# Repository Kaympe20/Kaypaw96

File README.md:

# Kaypaw96

<br>

A Southpaw 96% keyboard because numpads on the left are awesome
* They allow the keyboard to be centered on your desk.
* They let you use the mouse and numpad at the same time.
* They are plain more ergonomic.

---

[As featured on](https://highway.hackclub.com/projects/kaympe20/kaypaw96)

---

I made this keyboard because, as an ambidextrous person, I often feel like my left hand is under-utilized while I am doing productivity, coding, and gaming. I also use a 75% and sometimes miss having more keys, so I wanted to make a keyboard that gave you nearly every key of a regular keyboard, plus 4 additional macro keys for things like sleep.

## Pics

## CAD

The entire CAD workspace can be found on [Onshape](https://cad.onshape.com/documents/bc15378757c65db7b8fb3e3b/w/9f716e622823b7e5e5c4b7e3/e/b78d5af8ee98cae8cd027468?renderMode=0&uiState=688afe042b679217b95b0b97)

## BOM

| Item | Quantity | Price | Price After Taxes + Shipping |
|------|----------|-------|------------------------------|
[Assembled PCB](https://github.com/Kaympe20/Kaypaw96/tree/main/production) | 1 | $81.58 | $169.13
[3D Printed Case](https://github.com/Kaympe20/Kaypaw96/blob/main/cad/Case.step) | 1 | $0 | $0
[Cherry MX Switches](https://www.amazon.com/Glorious-Gaming-Hotswappable-Mechanical-Keyboards/dp/B0DCPCS6CP) (cheapest I could find after shipping) | 110 | $31.99 | $33.91
[Keycap Set](https://www.amazon.com/Keycaps-Doubleshot-Percent-Mechanical-Keyboard/dp/B0D1QVD55F) | 1 | $16.86 | $17.87
[NCP1117-3.3_SOT223](https://www.amazon.com/PMMCON-AMS1117-LM1117-Voltage-Regulator/dp/B0BNY8KM87) | 1 | $9.99 | $10.59
[M3 Hardware](https://www.amazon.com/420pcs-Premium-Printing-Assortment-Washers/dp/B0CSX4NX7R) | N/a | $6.99 | $7.41

Total: $238.91

Here's the parts I selected in JLCPCB:

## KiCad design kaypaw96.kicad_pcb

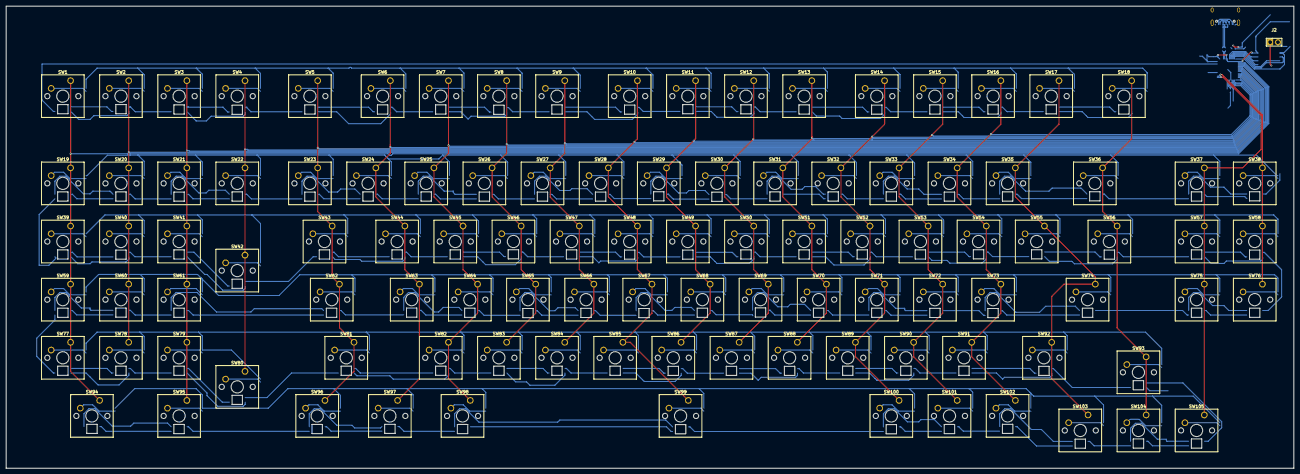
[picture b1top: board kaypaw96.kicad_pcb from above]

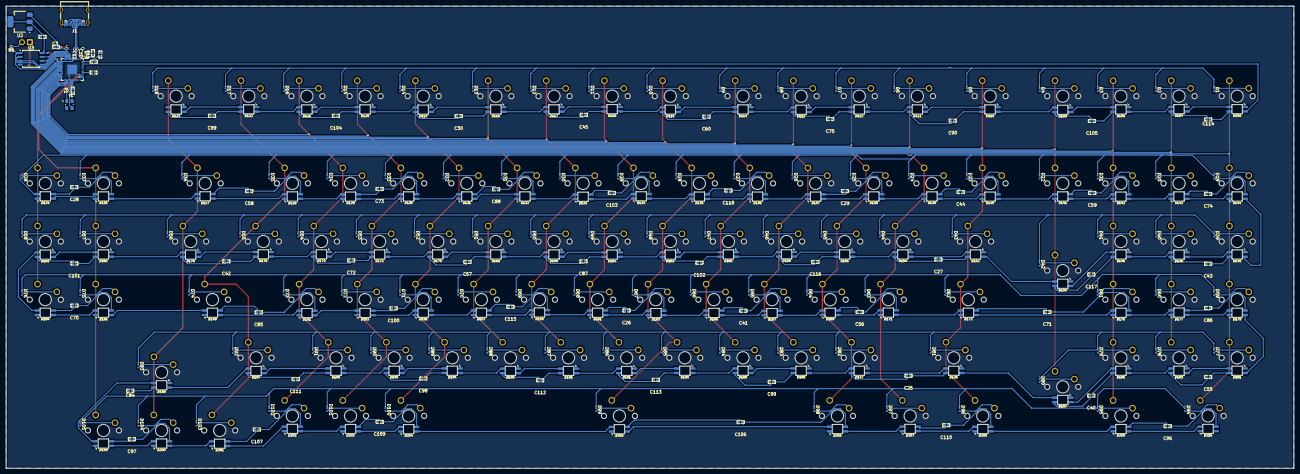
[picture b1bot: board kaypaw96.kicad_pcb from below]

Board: 2 copper layers, 421.9 x 151.4 mm, 388 parts (282 on the bottom side), 256 nets.

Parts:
C3: 10u; C0402
C8, C9, C10, C11, C12, C13, C14: 100n; C0402
C25, C26, C27, C28, C29, C30, C40, C41, C42, C43, C44, C45, C55, C56, C57, C58, C59, C60, C70, C71, C72, C73, C74, C75, C84, C85, C86, C87, C88, C89, C90, C96, C97, C98, C99, C100, C101, C102, C103, C104, C105, C106, C107, C109, C110, C111, C112, C113, C114, C115, C116, C117, C118: 0.1u; C0402
D1, D2, D3, D4, D5, D6, D7, D8, D9, D10, D11, D12, D13, D14, D15, D16, D17, D18, D19, D20, D21, D22, D23, D24, D25, D26, D27, D28, D29, D30, D31, D32, D33, D34, D35, D36, D37, D38, D39, D40, D41, D42, D43, D44, D45, D46, D47, D48, D49, D50, D51, D52, D53, D54, D55, D56, D57, D58, D59, D60, D61, D62, D63, D64, D65, D66, D67, D68, D69, D70, D71, D72, D73, D74, D75, D76, D77, D78, D79, D80, D81, D82, D83, D84, D85, D86, D87, D88, D89, D90, D91, D92, D93, D94, D95, D96, D97, D98, D99, D100, D101, D102, D103, D104, D105: D; RB161QS-40
D106, D107, D108, D109, D110, D111, D112, D113, D114, D115, D116, D117, D118, D119, D120, D121, D122, D123, D124, D125, D126, D127, D128, D129, D130, D131, D132, D133, D134, D135, D136, D137, D138, D139, D140, D141, D142, D143, D144, D145, D146, D147, D148, D149, D150, D151, D152, D153, D154, D155, D156, D157, D158, D159, D160, D161, D162, D163, D164, D165, D166, D167, D168, D169, D170, D171, D172, D173, D174, D175, D176, D177, D178, D179, D180, D181, D182, D183, D184, D185, D186, D187, D188, D189, D190, D191, D192, D193, D194, D195, D196, D197, D198, D199, D200, D201, D202, D203, D204, D205, D206, D207, D208, D209, D210: SK6812MINI; SK6812MINI-E
J1: USB_C_Receptacle_USB2.0_14P; USB_C_Receptacle_XKB_U262-16XN-4BVC11
J2: Conn_01x02; HDR-TH_2P-P2.54-V-M
R1, R6: 1k; R_0402_1005Metric
R2, R3: 5.1k; R_0402_1005Metric
R4, R5: 27.4; R_0402_1005Metric
SW1, SW2, SW3, SW4, SW5, SW6, SW7, SW8, SW9, SW10, SW11, SW12, SW13, SW14, SW15, SW16, SW17, SW18, SW19, SW20, SW21, SW22, SW23, SW24, SW25, SW26, SW27, SW28, SW29, SW30, SW31, SW32, SW33, SW34, SW35, SW36, SW37, SW38, SW39, SW40, SW41, SW42, SW43, SW44, SW45, SW46, SW47, SW48, SW49, SW50, SW51, SW52, SW53, SW54, SW55, SW56, SW57, SW58, SW59, SW60, SW61, SW62, SW63, SW64, SW65, SW66, SW67, SW68, SW69, SW70, SW71, SW72, SW73, SW74, SW75, SW76, SW77, SW78, SW79, SW80, SW81, SW82, SW83, SW84, SW85, SW86, SW87, SW88, SW89, SW90, SW91, SW92, SW93, SW94, SW95, SW96, SW97, SW98, SW99, SW100, SW101, SW102, SW103, SW104, SW105: SW_Push_45deg; SW_Cherry_MX_1.00u_PCB
U1: RP2040; QFN-56-1EP_7x7mm_P0.4mm_EP3.2x3.2mm
U2: NCP1117-3.3_SOT223; SOT-223-3_TabPin2
U3: W25Q128JVS; SOIC-8_5.3x5.3mm_P1.27mm
Y1: ABM8-272-T3; XTAL_ABM8-272-T3

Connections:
+1V1: U1.23 (DVDD), U1.45 (VREG_VOUT), U1.50 (DVDD)
+3.3V: C8.1, C9.1, C10.1, C11.1, C12.1, C13.1, C14.1, U1.1 (IOVDD), U1.10 (IOVDD), U1.22 (IOVDD), U1.33 (IOVDD), U1.42 (IOVDD), U1.43 (ADC_AVDD), U1.44 (VREG_IN), U1.48 (USB_VDD), U1.49 (IOVDD), U2.2 (VO), U3.8 (VCC)
+5V: C3.1, C25.1, C26.1, C27.1, C28.1, C29.1, C30.1, C40.1, C41.1, C42.1, C43.1, C44.1, C45.1, C55.1, C56.1, C57.1, C58.1, C59.1, C60.1, C70.1, C71.1, C72.1, C73.1, C74.1, C75.1, C84.1, C85.1, C86.1, C87.1, C88.1, C89.1, C90.1, C96.1, C97.1, C98.1, C99.1, C100.1, C101.1, C102.1, C103.1, C104.1, C105.1, C106.1, C107.1, C109.1, C110.1, C111.1, C112.1, C113.1, C114.1, C115.1, C116.1, C117.1, C118.1, D106.4 (VDD), D107.4 (VDD), D108.4 (VDD), D109.4 (VDD), D110.4 (VDD), D111.4 (VDD), D112.4 (VDD), D113.4 (VDD), D114.4 (VDD), D115.4 (VDD), D116.4 (VDD), D117.4 (VDD), D118.4 (VDD), D119.4 (VDD), D120.4 (VDD), D121.4 (VDD), D122.4 (VDD), D123.4 (VDD), D124.4 (VDD), D125.4 (VDD), D126.4 (VDD), D127.4 (VDD), D128.4 (VDD), D129.4 (VDD), D130.4 (VDD), D131.4 (VDD), D132.4 (VDD), D133.4 (VDD), D134.4 (VDD), D135.4 (VDD), D136.4 (VDD), D137.4 (VDD), D138.4 (VDD), D139.4 (VDD), D140.4 (VDD), D141.4 (VDD), D142.4 (VDD), D143.4 (VDD), D144.4 (VDD), D145.4 (VDD), D146.4 (VDD), D147.4 (VDD), D148.4 (VDD), D149.4 (VDD), D150.4 (VDD), D151.4 (VDD), D152.4 (VDD), D153.4 (VDD), D154.4 (VDD), D155.4 (VDD), D156.4 (VDD), D157.4 (VDD), D158.4 (VDD), D159.4 (VDD), D160.4 (VDD), D161.4 (VDD), D162.4 (VDD), D163.4 (VDD), D164.4 (VDD), D165.4 (VDD), D166.4 (VDD), D167.4 (VDD), D168.4 (VDD), D169.4 (VDD), D170.4 (VDD), D171.4 (VDD), D172.4 (VDD), D173.4 (VDD), D174.4 (VDD), D175.4 (VDD), D176.4 (VDD), D177.4 (VDD), D178.4 (VDD), D179.4 (VDD), D180.4 (VDD), D181.4 (VDD), D182.4 (VDD), D183.4 (VDD), D184.4 (VDD), D185.4 (VDD), D186.4 (VDD), D187.4 (VDD), D188.4 (VDD), D189.4 (VDD), D190.4 (VDD), D191.4 (VDD), D192.4 (VDD), D193.4 (VDD), D194.4 (VDD), D195.4 (VDD), D196.4 (VDD), D197.4 (VDD), D198.4 (VDD), D199.4 (VDD), D200.4 (VDD), D201.4 (VDD), D202.4 (VDD), D203.4 (VDD), D204.4 (VDD), D205.4 (VDD), D206.4 (VDD), D207.4 (VDD), D208.4 (VDD), D209.4 (VDD), D210.4 (VDD), J1.A4 (VBUS), J1.A9 (VBUS), J1.B4 (VBUS), J1.B9 (VBUS), U2.3 (VI)
/QSPI_SCLK: U1.52 (QSPI_SCLK), U3.6 (CLK)
/QSPI_SD0: U1.53 (QSPI_SD0), U3.5 (DI/IO_{0})
/QSPI_SD1: U1.55 (QSPI_SD1), U3.2 (DO/IO_{1})
/QSPI_SD2: U1.54 (QSPI_SD2), U3.3 (~WP/IO_{2})
/QSPI_SD3: U1.51 (QSPI_SD3), U3.7 (~HOLD/~RESET/IO_{3})
/QSPI_SS: R6.2, U1.56 (QSPI_SS), U3.1 (~CS)
Col 1: SW1.1, SW19.1, SW39.1, SW59.1, SW77.1, SW94.1, U1.2 (GPIO0)
Col 2: SW2.1, SW20.1, SW40.1, SW60.1, SW78.1, U1.3 (GPIO1)
Col 3: SW3.1, SW21.1, SW41.1, SW61.1, SW79.1, SW95.1, U1.4 (GPIO2)
Col 4: SW4.1, SW22.1, SW42.1, SW80.1, U1.5 (GPIO3)
Col 5: SW5.1, SW23.1, SW43.1, SW62.1, SW81.1, SW96.1, U1.6 (GPIO4)
Col 6: SW6.1, SW24.1, SW44.1, SW63.1, SW97.1, U1.7 (GPIO5)
Col 7: SW7.1, SW25.1, SW45.1, SW64.1, SW82.1, SW98.1, U1.8 (GPIO6)
Col 8: SW8.1, SW26.1, SW46.1, SW65.1, SW83.1, U1.9 (GPIO7)
Col 9: SW9.1, SW27.1, SW47.1, SW66.1, SW84.1, U1.11 (GPIO8)
Col 10: SW10.1, SW28.1, SW48.1, SW67.1, SW85.1, SW99.1, U1.12 (GPIO9)
Col 11: SW11.1, SW29.1, SW49.1, SW68.1, SW86.1, U1.13 (GPIO10)
Col 12: SW12.1, SW30.1, SW50.1, SW69.1, SW87.1, U1.14 (GPIO11)
Col 13: SW13.1, SW31.1, SW51.1, SW70.1, SW88.1, U1.15 (GPIO12)
Col 14: SW14.1, SW32.1, SW52.1, SW71.1, SW89.1, SW100.1, U1.16 (GPIO13)
Col 15: SW15.1, SW33.1, SW53.1, SW72.1, SW90.1, SW101.1, U1.17 (GPIO14)
Col 16: SW16.1, SW34.1, SW54.1, SW73.1, SW91.1, SW102.1, U1.18 (GPIO15)
Col 17: SW17.1, SW35.1, SW55.1, SW74.1, SW92.1, SW103.1, U1.27 (GPIO16)
Col 18: SW18.1, SW36.1, SW56.1, SW93.1, SW104.1, U1.28 (GPIO17)
Col 19: SW37.1, SW57.1, SW75.1, SW105.1, U1.29 (GPIO18)
Col 20: SW38.1, SW58.1, SW76.1, U1.30 (GPIO19)
D+: J1.A6 (D+), J1.B6 (D+), R4.1
D-: J1.A7 (D-), J1.B7 (D-), R5.1
GND: C3.2, C8.2, C9.2, C10.2, C11.2, C12.2, C13.2, C14.2, C25.2, C26.2, C27.2, C28.2, C29.2, C30.2, C40.2, C41.2, C42.2, C43.2, C44.2, C45.2, C55.2, C56.2, C57.2, C58.2, C59.2, C60.2, C70.2, C71.2, C72.2, C73.2, C74.2, C75.2, C84.2, C85.2, C86.2, C87.2, C88.2, C89.2, C90.2, C96.2, C97.2, C98.2, C99.2, C100.2, C101.2, C102.2, C103.2, C104.2, C105.2, C106.2, C107.2, C109.2, C110.2, C111.2, C112.2, C113.2, C114.2, C115.2, C116.2, C117.2, C118.2, D106.2 (VSS), D107.2 (VSS), D108.2 (VSS), D109.2 (VSS), D110.2 (VSS), D111.2 (VSS), D112.2 (VSS), D113.2 (VSS), D114.2 (VSS), D115.2 (VSS), D116.2 (VSS), D117.2 (VSS), D118.2 (VSS), D119.2 (VSS), D120.2 (VSS), D121.2 (VSS), D122.2 (VSS), D123.2 (VSS), D124.2 (VSS), D125.2 (VSS), D126.2 (VSS), D127.2 (VSS), D128.2 (VSS), D129.2 (VSS), D130.2 (VSS), D131.2 (VSS), D132.2 (VSS), D133.2 (VSS), D134.2 (VSS), D135.2 (VSS), D136.2 (VSS), D137.2 (VSS), D138.2 (VSS), D139.2 (VSS), D140.2 (VSS), D141.2 (VSS), D142.2 (VSS), D143.2 (VSS), D144.2 (VSS), D145.2 (VSS), D146.2 (VSS), D147.2 (VSS), D148.2 (VSS), D149.2 (VSS), D150.2 (VSS), D151.2 (VSS), D152.2 (VSS), D153.2 (VSS), D154.2 (VSS), D155.2 (VSS), D156.2 (VSS), D157.2 (VSS), D158.2 (VSS), D159.2 (VSS), D160.2 (VSS), D161.2 (VSS), D162.2 (VSS), D163.2 (VSS), D164.2 (VSS), D165.2 (VSS), D166.2 (VSS), D167.2 (VSS), D168.2 (VSS), D169.2 (VSS), D170.2 (VSS), D171.2 (VSS), D172.2 (VSS), D173.2 (VSS), D174.2 (VSS), D175.2 (VSS), D176.2 (VSS), D177.2 (VSS), D178.2 (VSS), D179.2 (VSS), D180.2 (VSS), D181.2 (VSS), D182.2 (VSS), D183.2 (VSS), D184.2 (VSS), D185.2 (VSS), D186.2 (VSS), D187.2 (VSS), D188.2 (VSS), D189.2 (VSS), D190.2 (VSS), D191.2 (VSS), D192.2 (VSS), D193.2 (VSS), D194.2 (VSS), D195.2 (VSS), D196.2 (VSS), D197.2 (VSS), D198.2 (VSS), D199.2 (VSS), D200.2 (VSS), D201.2 (VSS), D202.2 (VSS), D203.2 (VSS), D204.2 (VSS), D205.2 (VSS), D206.2 (VSS), D207.2 (VSS), D208.2 (VSS), D209.2 (VSS), D210.2 (VSS), J1.A1 (GND), J1.A12 (GND), J1.B1 (GND), J1.B12 (GND), J1.S1 (SHIELD), J2.1, R2.2, R3.2, U1.19 (TESTEN), U1.57 (GND), U2.1 (GND), U3.4 (GND), Y1.2 (GND), Y1.4 (GND)
NEO: D106.3 (DIN), U1.40 (GPIO28_ADC2)
unnamed: R1.1, Y1.3
unnamed: D1.2 (A), SW1.2
unnamed: D2.2 (A), SW2.2
unnamed: D3.2 (A), SW3.2
unnamed: D4.2 (A), SW4.2
unnamed: D5.2 (A), SW5.2
unnamed: D6.2 (A), SW6.2
unnamed: D7.2 (A), SW7.2
unnamed: D8.2 (A), SW8.2
unnamed: D9.2 (A), SW9.2
unnamed: D10.2 (A), SW10.2
unnamed: D11.2 (A), SW11.2
unnamed: D12.2 (A), SW12.2
unnamed: D13.2 (A), SW13.2
unnamed: D14.2 (A), SW14.2
unnamed: D15.2 (A), SW15.2
unnamed: D16.2 (A), SW16.2
unnamed: D17.2 (A), SW17.2
unnamed: D18.2 (A), SW18.2
unnamed: D19.2 (A), SW19.2
unnamed: D20.2 (A), SW20.2
unnamed: D21.2 (A), SW21.2
unnamed: D22.2 (A), SW22.2
unnamed: D23.2 (A), SW23.2
unnamed: D24.2 (A), SW24.2
unnamed: D25.2 (A), SW25.2
unnamed: D26.2 (A), SW26.2
unnamed: D27.2 (A), SW27.2
unnamed: D28.2 (A), SW28.2
unnamed: D29.2 (A), SW29.2
unnamed: D30.2 (A), SW30.2
unnamed: D31.2 (A), SW31.2
unnamed: D32.2 (A), SW32.2
unnamed: D33.2 (A), SW33.2
unnamed: D34.2 (A), SW34.2
unnamed: D35.2 (A), SW35.2
unnamed: D36.2 (A), SW36.2
unnamed: D37.2 (A), SW37.2
unnamed: D38.2 (A), SW38.2
unnamed: D39.2 (A), SW39.2
unnamed: D40.2 (A), SW40.2
unnamed: D41.2 (A), SW41.2
unnamed: D42.2 (A), SW42.2
unnamed: D43.2 (A), SW43.2
unnamed: D44.2 (A), SW44.2
unnamed: D45.2 (A), SW45.2
unnamed: D46.2 (A), SW46.2
unnamed: D47.2 (A), SW47.2
unnamed: D48.2 (A), SW48.2
unnamed: D49.2 (A), SW49.2
unnamed: D50.2 (A), SW50.2
unnamed: D51.2 (A), SW51.2
unnamed: D52.2 (A), SW52.2
unnamed: D53.2 (A), SW53.2
unnamed: D54.2 (A), SW54.2
unnamed: D55.2 (A), SW55.2
unnamed: D56.2 (A), SW56.2
unnamed: D57.2 (A), SW57.2
unnamed: D58.2 (A), SW58.2
unnamed: D59.2 (A), SW59.2
unnamed: D60.2 (A), SW60.2
unnamed: D61.2 (A), SW61.2
unnamed: D62.2 (A), SW62.2
unnamed: D63.2 (A), SW63.2
unnamed: D64.2 (A), SW64.2
unnamed: D65.2 (A), SW65.2
unnamed: D66.2 (A), SW66.2
unnamed: D67.2 (A), SW67.2
unnamed: D68.2 (A), SW68.2
unnamed: D69.2 (A), SW69.2
unnamed: D70.2 (A), SW70.2
unnamed: D71.2 (A), SW71.2
unnamed: D72.2 (A), SW72.2
unnamed: D73.2 (A), SW73.2
unnamed: D74.2 (A), SW74.2
unnamed: D75.2 (A), SW75.2
unnamed: D76.2 (A), SW76.2
unnamed: D77.2 (A), SW77.2
unnamed: D78.2 (A), SW78.2
unnamed: D79.2 (A), SW79.2
unnamed: D80.2 (A), SW80.2
unnamed: D81.2 (A), SW81.2
unnamed: D82.2 (A), SW82.2
unnamed: D83.2 (A), SW83.2
unnamed: D84.2 (A), SW84.2
unnamed: D85.2 (A), SW85.2
unnamed: D86.2 (A), SW86.2
unnamed: D87.2 (A), SW87.2
unnamed: D88.2 (A), SW88.2
unnamed: D89.2 (A), SW89.2
unnamed: D90.2 (A), SW90.2
unnamed: D91.2 (A), SW91.2
unnamed: D92.2 (A), SW92.2
unnamed: D93.2 (A), SW93.2
unnamed: D94.2 (A), SW94.2
unnamed: D95.2 (A), SW95.2
unnamed: D96.2 (A), SW96.2
unnamed: D97.2 (A), SW97.2
unnamed: D98.2 (A), SW98.2
unnamed: D99.2 (A), SW99.2
unnamed: D100.2 (A), SW100.2
unnamed: D101.2 (A), SW101.2
unnamed: D102.2 (A), SW102.2
unnamed: D103.2 (A), SW103.2
unnamed: D104.2 (A), SW104.2
unnamed: D105.2 (A), SW105.2
unnamed: D106.1 (DOUT), D107.3 (DIN)
unnamed: D107.1 (DOUT), D108.3 (DIN)
unnamed: D108.1 (DOUT), D109.3 (DIN)
unnamed: D109.1 (DOUT), D110.3 (DIN)
unnamed: D110.1 (DOUT), D111.3 (DIN)
unnamed: D111.1 (DOUT), D112.3 (DIN)
unnamed: D112.1 (DOUT), D113.3 (DIN)
unnamed: D113.1 (DOUT), D114.3 (DIN)
unnamed: D114.1 (DOUT), D115.3 (DIN)
unnamed: D115.1 (DOUT), D116.3 (DIN)
unnamed: D116.1 (DOUT), D117.3 (DIN)
unnamed: D117.1 (DOUT), D118.3 (DIN)
unnamed: D118.1 (DOUT), D119.3 (DIN)
unnamed: D119.1 (DOUT), D120.3 (DIN)
unnamed: D120.1 (DOUT), D121.3 (DIN)
unnamed: D121.1 (DOUT), D122.3 (DIN)
unnamed: D122.1 (DOUT), D123.3 (DIN)
unnamed: D123.1 (DOUT), D124.3 (DIN)
unnamed: D124.1 (DOUT), D125.3 (DIN)
unnamed: D125.1 (DOUT), D127.3 (DIN)
unnamed: D126.3 (DIN), D187.1 (DOUT)
unnamed: D126.1 (DOUT), D147.3 (DIN)
unnamed: D127.1 (DOUT), D128.3 (DIN)
unnamed: D128.1 (DOUT), D129.3 (DIN)
unnamed: D129.1 (DOUT), D130.3 (DIN)
unnamed: D130.1 (DOUT), D131.3 (DIN)
unnamed: D131.1 (DOUT), D132.3 (DIN)
unnamed: D132.1 (DOUT), D133.3 (DIN)
unnamed: D133.1 (DOUT), D134.3 (DIN)
unnamed: D134.1 (DOUT), D135.3 (DIN)
unnamed: D135.1 (DOUT), D136.3 (DIN)
unnamed: D136.1 (DOUT), D137.3 (DIN)
unnamed: D137.1 (DOUT), D138.3 (DIN)
unnamed: D138.1 (DOUT), D139.3 (DIN)
unnamed: D139.1 (DOUT), D140.3 (DIN)
unnamed: D140.1 (DOUT), D141.3 (DIN)
unnamed: D141.1 (DOUT), D142.3 (DIN)
unnamed: D142.1 (DOUT), D143.3 (DIN)
unnamed: D143.1 (DOUT), D144.3 (DIN)
unnamed: D144.1 (DOUT), D145.3 (DIN)
unnamed: D145.1 (DOUT), D146.3 (DIN)
unnamed: D146.1 (DOUT), D148.3 (DIN)
unnamed: D147.1 (DOUT), D188.3 (DIN)
unnamed: D148.1 (DOUT), D150.3 (DIN)
unnamed: D149.3 (DIN), D186.1 (DOUT)
unnamed: D149.1 (DOUT), D151.3 (DIN)
unnamed: D150.1 (DOUT), D152.3 (DIN)
unnamed: D151.1 (DOUT), D153.3 (DIN)
unnamed: D152.1 (DOUT), D154.3 (DIN)
unnamed: D153.1 (DOUT), D155.3 (DIN)
unnamed: D154.1 (DOUT), D156.3 (DIN)
unnamed: D155.1 (DOUT), D157.3 (DIN)
unnamed: D156.1 (DOUT), D158.3 (DIN)
unnamed: D157.1 (DOUT), D159.3 (DIN)
unnamed: D158.1 (DOUT), D160.3 (DIN)
unnamed: D159.1 (DOUT), D161.3 (DIN)
unnamed: D160.1 (DOUT), D162.3 (DIN)
unnamed: D161.1 (DOUT), D163.3 (DIN)
unnamed: D162.1 (DOUT), D164.3 (DIN)
unnamed: D163.1 (DOUT), D165.3 (DIN)
unnamed: D164.1 (DOUT), D166.3 (DIN)
unnamed: D165.1 (DOUT), D167.3 (DIN)
unnamed: D166.1 (DOUT), D168.3 (DIN)
unnamed: D167.1 (DOUT), D169.3 (DIN)
unnamed: D168.1 (DOUT), D170.3 (DIN)
unnamed: D169.1 (DOUT), D171.3 (DIN)
unnamed: D170.1 (DOUT), D172.3 (DIN)
unnamed: D171.1 (DOUT), D173.3 (DIN)
unnamed: D172.1 (DOUT), D174.3 (DIN)
unnamed: D173.1 (DOUT), D175.3 (DIN)
unnamed: D174.1 (DOUT), D176.3 (DIN)
unnamed: D175.1 (DOUT), D177.3 (DIN)
unnamed: D176.1 (DOUT), D178.3 (DIN)
unnamed: D177.1 (DOUT), D179.3 (DIN)
unnamed: D178.1 (DOUT), D180.3 (DIN)
unnamed: D179.1 (DOUT), D181.3 (DIN)
unnamed: D180.1 (DOUT), D182.3 (DIN)
unnamed: D181.1 (DOUT), D183.3 (DIN)
unnamed: D182.1 (DOUT), D184.3 (DIN)
unnamed: D183.1 (DOUT), D185.3 (DIN)
unnamed: D184.1 (DOUT), D186.3 (DIN)
unnamed: D185.1 (DOUT), D187.3 (DIN)
unnamed: D188.1 (DOUT), D189.3 (DIN)
unnamed: D189.1 (DOUT), D190.3 (DIN)
unnamed: D190.1 (DOUT), D191.3 (DIN)
unnamed: D191.1 (DOUT), D192.3 (DIN)
unnamed: D192.1 (DOUT), D193.3 (DIN)
unnamed: D193.1 (DOUT), D194.3 (DIN)
unnamed: D194.1 (DOUT), D195.3 (DIN)
unnamed: D195.1 (DOUT), D196.3 (DIN)
unnamed: D196.1 (DOUT), D197.3 (DIN)
unnamed: D197.1 (DOUT), D198.3 (DIN)
unnamed: D198.1 (DOUT), D199.3 (DIN)
unnamed: D199.1 (DOUT), D200.3 (DIN)
unnamed: D200.1 (DOUT), D201.3 (DIN)
unnamed: D201.1 (DOUT), D202.3 (DIN)
unnamed: D202.1 (DOUT), D203.3 (DIN)
unnamed: D203.1 (DOUT), D204.3 (DIN)
unnamed: D204.1 (DOUT), D205.3 (DIN)
unnamed: D205.1 (DOUT), D206.3 (DIN)
unnamed: D206.1 (DOUT), D207.3 (DIN)
unnamed: D207.1 (DOUT), D208.3 (DIN)
unnamed: D208.1 (DOUT), D209.3 (DIN)
unnamed: D209.1 (DOUT), D210.3 (DIN)
unnamed: J1.A5 (CC1), R2.1
unnamed: J1.B5 (CC2), R3.1
unnamed: J2.2, R6.1
unnamed: R5.2, U1.46 (USB_DM)
unnamed: R4.2, U1.47 (USB_DP)
unnamed: U1.20 (XIN), Y1.1
unnamed: R1.2, U1.21 (XOUT)
Row 1: D1.1 (K), D2.1 (K), D3.1 (K), D4.1 (K), D5.1 (K), D6.1 (K), D7.1 (K), D8.1 (K), D9.1 (K), D10.1 (K), D11.1 (K), D12.1 (K), D13.1 (K), D14.1 (K), D15.1 (K), D16.1 (K), D17.1 (K), D18.1 (K), U1.31 (GPIO20)
Row 2: D19.1 (K), D20.1 (K), D21.1 (K), D22.1 (K), D23.1 (K), D24.1 (K), D25.1 (K), D26.1 (K), D27.1 (K), D28.1 (K), D29.1 (K), D30.1 (K), D31.1 (K), D32.1 (K), D33.1 (K), D34.1 (K), D35.1 (K), D36.1 (K), D37.1 (K), D38.1 (K), U1.32 (GPIO21)
Row 3: D39.1 (K), D40.1 (K), D41.1 (K), D42.1 (K), D43.1 (K), D44.1 (K), D45.1 (K), D46.1 (K), D47.1 (K), D48.1 (K), D49.1 (K), D50.1 (K), D51.1 (K), D52.1 (K), D53.1 (K), D54.1 (K), D55.1 (K), D56.1 (K), D57.1 (K), D58.1 (K), U1.34 (GPIO22)
Row 4: D59.1 (K), D60.1 (K), D61.1 (K), D62.1 (K), D63.1 (K), D64.1 (K), D65.1 (K), D66.1 (K), D67.1 (K), D68.1 (K), D69.1 (K), D70.1 (K), D71.1 (K), D72.1 (K), D73.1 (K), D74.1 (K), D75.1 (K), D76.1 (K), U1.35 (GPIO23)
Row 5: D77.1 (K), D78.1 (K), D79.1 (K), D80.1 (K), D81.1 (K), D82.1 (K), D83.1 (K), D84.1 (K), D85.1 (K), D86.1 (K), D87.1 (K), D88.1 (K), D89.1 (K), D90.1 (K), D91.1 (K), D92.1 (K), D93.1 (K), U1.36 (GPIO24)
Row 6: D94.1 (K), D95.1 (K), D96.1 (K), D97.1 (K), D98.1 (K), D99.1 (K), D100.1 (K), D101.1 (K), D102.1 (K), D103.1 (K), D104.1 (K), D105.1 (K), U1.37 (GPIO25)

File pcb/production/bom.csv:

Designator,Footprint,Quantity,Value,LCSC Part #
"C1, C2",C0402,2,15p,
"C10, C11, C12, C13, C14, C16, C6, C7, C8, C9",C0402,10,100n,
"C100, C101, C102, C103, C104, C105, C106, C107, C109, C110, C111, C112, C113, C114, C115, C116, C117, C118, C25, C26, C27, C28, C29, C30, C40, C41, C42, C43, C44, C45, C55, C56, C57, C58, C59, C60, C70, C71, C72, C73, C74, C75, C84, C85, C86, C87, C88, C89, C90, C96, C97, C98, C99",C0402,53,0.1u,
"C15, C5",C0402,2,1u,
"C3, C4",C0402,2,10u,
"D1, D10, D100, D101, D102, D103, D104, D105, D11, D12, D13, D14, D15, D16, D17, D18, D19, D2, D20, D21, D22, D23, D24, D25, D26, D27, D28, D29, D3, D30, D31, D32, D33, D34, D35, D36, D37, D38, D39, D4, D40, D41, D42, D43, D44, D45, D46, D47, D48, D49, D5, D50, D51, D52, D53, D54, D55, D56, D57, D58, D59, D6, D60, D61, D62, D63, D64, D65, D66, D67, D68, D69, D7, D70, D71, D72, D73, D74, D75, D76, D77, D78, D79, D8, D80, D81, D82, D83, D84, D85, D86, D87, D88, D89, D9, D90, D91, D92, D93, D94, D95, D96, D97, D98, D99",RB161QS-40,105,D,
"D106, D107, D108, D109, D110, D111, D112, D113, D114, D115, D116, D117, D118, D119, D120, D121, D122, D123, D124, D125, D126, D127, D128, D129, D130, D131, D132, D133, D134, D135, D136, D137, D138, D139, D140, D141, D142, D143, D144, D145, D146, D147, D148, D149, D150, D151, D152, D153, D154, D155, D156, D157, D158, D159, D160, D161, D162, D163, D164, D165, D166, D167, D168, D169, D170, D171, D172, D173, D174, D175, D176, D177, D178, D179, D180, D181, D182, D183, D184, D185, D186, D187, D188, D189, D190, D191, D192, D193, D194, D195, D196, D197, D198, D199, D200, D201, D202, D203, D204, D205, D206, D207, D208, D209, D210",SK6812MINI-E,105,SK6812MINI,
J1,USB_C_Receptacle_XKB_U262-16XN-4BVC11,1,USB_C_Receptacle_USB2.0_14P,
J2,HDR-TH_2P-P2.54-V-M,1,Conn_01x02,
"R1, R6",0402,2,1k,
"R2, R3",0402,2,5.1k,
"R4, R5",0402,2,27.4,
"SW1, SW10, SW100, SW101, SW102, SW103, SW104, SW105, SW11, SW12, SW13, SW14, SW15, SW16, SW17, SW18, SW19, SW2, SW20, SW21, SW22, SW23, SW24, SW25, SW26, SW27, SW28, SW29, SW3, SW30, SW31, SW32, SW33, SW34, SW35, SW37, SW38, SW39, SW4, SW40, SW41, SW43, SW44, SW45, SW46, SW47, SW48, SW49, SW5, SW50, SW51, SW52, SW53, SW54, SW55, SW56, SW57, SW58, SW59, SW6, SW60, SW61, SW62, SW63, SW64, SW65, SW66, SW67, SW68, SW69, SW7, SW70, SW71, SW72, SW73, SW75, SW76, SW77, SW78, SW79, SW8, SW82, SW83, SW84, SW85, SW86, SW87, SW88, SW89, SW9, SW90, SW91, SW92, SW93, SW94, SW95, SW96, SW97, SW98",SW_Cherry_MX_1.00u_PCB,99,SW_Push_45deg,
"SW36, SW74, SW81",SW_Cherry_MX_2.00u_PCB,3,SW_Push_45deg,
"SW42, SW80",SW_Cherry_MX_2.00u_Vertical_PCB,2,SW_Push_45deg,
SW99,SW_Cherry_MX_6.25u_PCB,1,SW_Push_45deg,
U1,QFN-56-1EP_7x7mm_P0.4mm_EP3.2x3.2mm,1,RP2040,
U2,SOT-223-3_TabPin2,1,NCP1117-3.3_SOT223,
U3,SOIC-8_5.3x5.3mm_P1.27mm,1,W25Q128JVS,
Y1,XTAL_ABM8-272-T3,1,ABM8-272-T3,

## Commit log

2025-07-04 Add auto_saved_files to gitignore
2025-07-04 Add JOURNAL.md
2025-07-04 Add autosave to KiCAD
2025-07-04 Add more journal entries
2025-07-04 Finish out RP2040 setup
2025-07-05 Add neopixels
2025-07-05 Add all imports
2025-07-05 Add capacitors for the neopixels
2025-07-05 Add footprints for everything
2025-07-06 Start PCB design
2025-07-06 Add all neopixels
2025-07-06 Add more capacitors
2025-07-06 Update JOURNAL with capacitors
2025-07-06 Expand .gitignore
2025-07-06 remove kicad_prl from gitignore
2025-07-25 Update Production files
2025-07-26 Route rows and cols as well as getting microcontroller and accessories wired up
2025-07-26 Finish PCB design
2025-07-27 Finish PCB (for real this time)
2025-07-28 Add STEP file
2025-07-30 Begin CAD and adjust mounting holes
2025-07-31 Update CAD to status as of 7/30/2025
2025-07-31 Do Firmware
2025-07-31 Move PCB to pcb/
2025-07-31 Update PCB
2025-07-31 Add production
2025-07-31 Remove csv from gitignore
2025-07-31 Add CAD
2025-07-31 Add changes needed before submission
2025-07-31 Add required README changes
2025-07-31 Add dates to JOURNAL.md
